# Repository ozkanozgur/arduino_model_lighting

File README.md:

# Model Lighting for Plastic or Diecast models.

You can make lighting for your plastic or diecast models.

Arduino project files, KiCad PCB design files are in this project.

If you don't want to use reed relays, you can replace reed relay with pullup buttons, or pullup short circuits. If you choose pullup buttons or pullup shortcircuits, you need use codes in "without-reed-relays" branch.

P.S.: Please, test circuit on breadboard before make/create final circuit.

### Complete component list is below.

- 1 x Arduino Uno
- 1 x Extra AT Mega 328 P Series Chip
- 12 x White LED (if neccessary for project you can use warm white led.)
- 4 x Red LED
- 4 x Yellow LED
- 10 x 470 ohm SMD Resistor (You can use 330 ohm.)
- 1 x Push Button
- 5 x Magnetic Reed Relay
- 5 x Neodium Magnet (I have used 3mm disc.)
- 2 x 22pF Capasitor
- 1 x 16.000 MHz Crystal
- 1 x 1838B IR Receiver
- 1 x 38KHz IR Remote Controller

### IR Remote Controller Button Functions

- OK => System on/off
- 1 => Parking lights on/off
- 2 => Dipped beam on/off
- 3 => High beam on/off
- 4 => Left turn signal on/off
- 5 => Right turn signal on/off
- 6 => Brake ligth on/off
- 7 => Hazard warning ligths on/off
- 8 => Reverse light on/off

# Plastik yada Diecast Modeller İçin Aydınlatma.

Bu projeyi kullanarak plastik yada diecast modellerinize uzaktan kumanda kontrollü ışıklandırma yapabilirsiniz.

Arduino proje dosyaları ve KiCad baskı devre tasarım dosyaları dahildir.

Eğer reed röleler yerine pullup button yada pullup kısa devre yapmak isterseniz, "without-reed-relays" branchi içerisindeki kodları kullanmanız gerekmektedir.

NOT: Lütfen devrenin baskı halini yapmadan önce breadboard üzerinde testlerinizi yapın.

### Komponent Listesi

- 1 x Arduino Uno
- 1 x Ekstra AT Mega 328 P Serisi Entegre Çip
- 12 x Beyaz LED (Projenize göre gün ışığı led de olabilir.)
- 4 x Kırmızı LED
- 4 x Sarı LED
- 10 x 470 ohm SMD Direnç (330 ohm da kullanılabilir.)
- 1 x Push Button
- 5 x Magnetic Reed Röle
- 5 x Neodium Mıknatıs (Ben 3mm yuvarlak olanlardan kullandım.)
- 2 x 22pF Kondansatör
- 1 x 16.000 MHz Kristal
- 1 x 1838B IR Alıcı
- 1 x 38KHz IR Uzaktan Kumanda

### IR Uzaktan Kumanda DÜğme Fonksiyonları

- OK => Sistem aç/kapat
- 1 => Parklar aç/kapat
- 2 => Kısalar aç/kapat
- 3 => Uzunlar aç/kapat
- 4 => Sol sinyal aç/kapat
- 5 => Sağ sinyal aç/kapat
- 6 => Fren lambası aç/kapat
- 7 => Dörtlüler aç/kapat
- 8 => Geri vites lambası aç/kapat
- Sol Ok => Sol sinyal aç/kapat
- Sağ Ok => Sağ sinyal aç/kapat

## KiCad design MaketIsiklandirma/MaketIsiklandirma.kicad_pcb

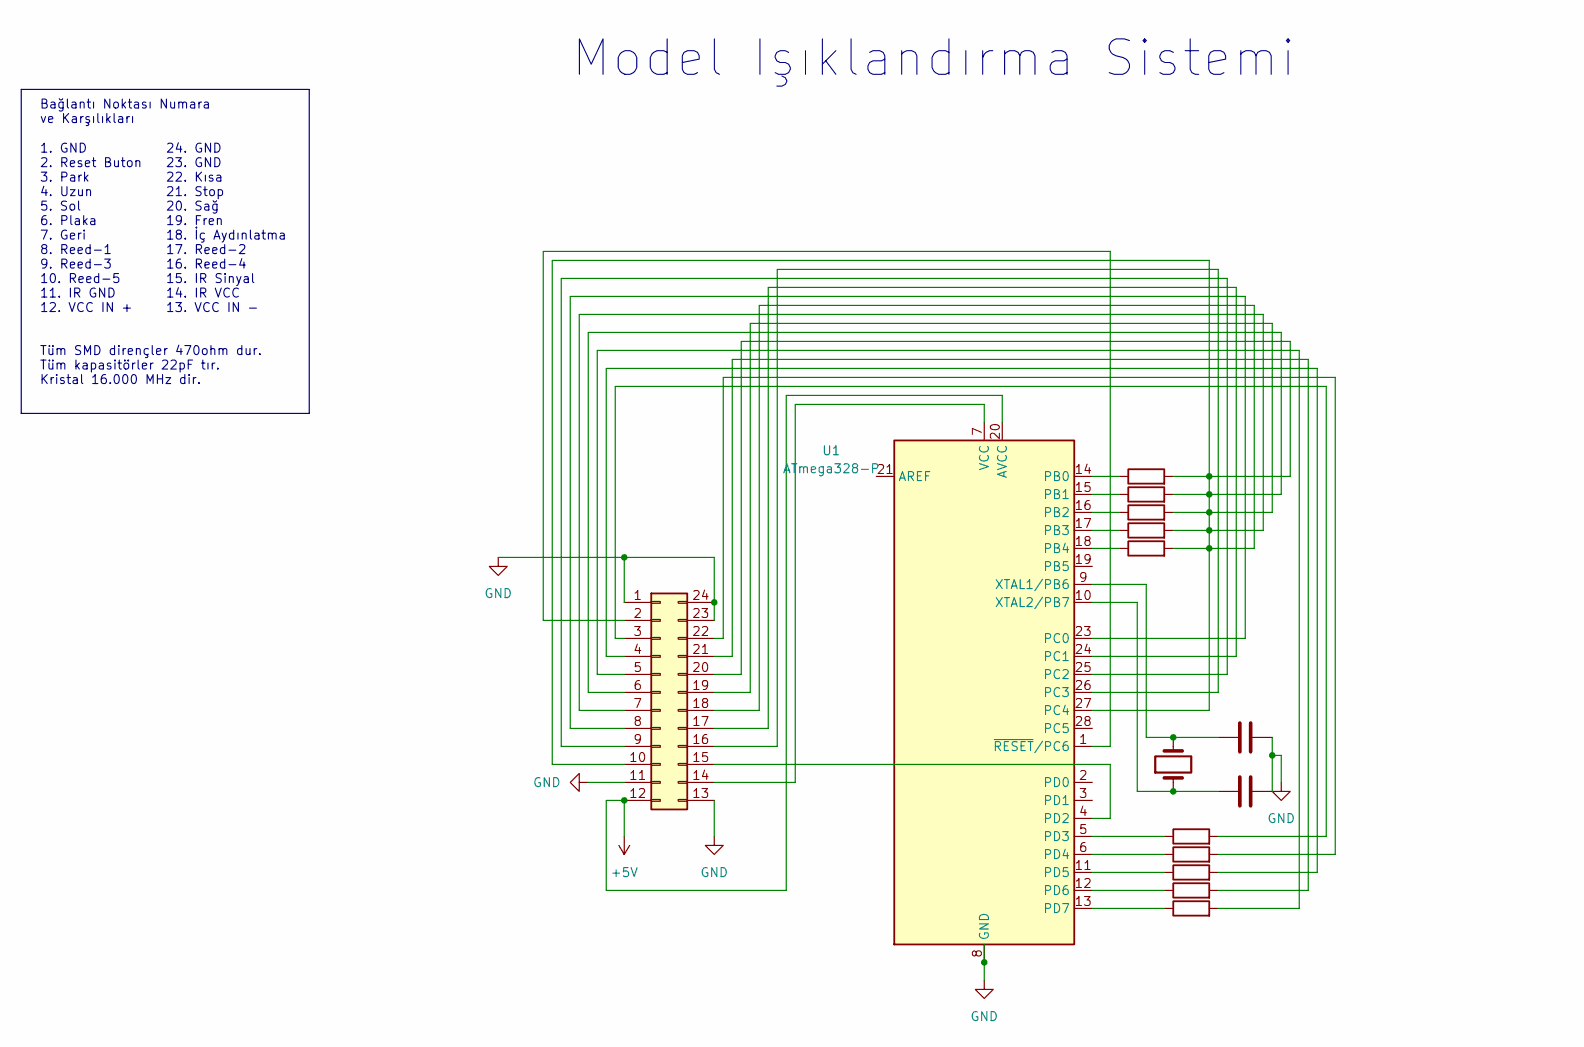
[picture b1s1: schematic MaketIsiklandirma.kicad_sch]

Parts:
C1, C2: C; C_Disc_D8.0mm_W5.0mm_P5.00mm
J3: Conn_02x12_Counter_Clockwise; IDC-Header_2x12_P2.54mm_Vertical
R1, R2, R3, R4, R5, R6, R7, R8, R9, R10: R; R_2512_6332Metric_Pad1.40x3.35mm_HandSolder
U1: ATmega328-P; DIP-28_W7.62mm
Y1: Crystal; Crystal_HC49-U_Vertical

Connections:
+5V: J3.12, U1.20 (AVCC)
unnamed: J3.3, R1.2
unnamed: J3.4, R3.2
unnamed: J3.5, R5.2
unnamed: J3.8, U1.23 (PC0)
unnamed: J3.9, U1.25 (PC2)
unnamed: J3.6, J3.7, J3.10, J3.18, J3.19, J3.20, R6.2, R7.2, R8.2, R9.2, R10.2, U1.27 (PC4)
unnamed: J3.14, U1.7 (VCC)
unnamed: J3.15, U1.4 (PD2)
unnamed: J3.16, U1.26 (PC3)
unnamed: J3.17, U1.24 (PC1)
unnamed: J3.21, R4.2
unnamed: J3.22, R2.2
unnamed: R10.1, U1.14 (PB0)
unnamed: R9.1, U1.15 (PB1)
unnamed: R8.1, U1.16 (PB2)
unnamed: R7.1, U1.17 (PB3)
unnamed: R6.1, U1.18 (PB4)
unnamed: R1.1, U1.5 (PD3)
unnamed: R2.1, U1.6 (PD4)
unnamed: R3.1, U1.11 (PD5)
unnamed: R4.1, U1.12 (PD6)
unnamed: R5.1, U1.13 (PD7)
unnamed: C2.1, U1.9 (XTAL1/PB6), Y1.2
unnamed: C1.1, U1.10 (XTAL2/PB7), Y1.1

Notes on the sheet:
Bağlantı Noktası Numara ve Karşılıkları
24. GND 23. GND 22. Kısa 21. Stop 20. Sağ 19. Fren 18. İç Aydınlatma 17. Reed-2 16. Reed-4 15. IR Sinyal 14. IR VCC 13. VCC IN -
Model Işıklandırma Sistemi
Tüm SMD dirençler 470ohm dur. Tüm kapasitörler 22pF tır. Kristal 16.000 MHz dir.
1. GND 2. Reset Buton 3. Park 4. Uzun 5. Sol 6. Plaka 7. Geri 8. Reed-1 9. Reed-3 10. Reed-5 11. IR GND 12. VCC IN +

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
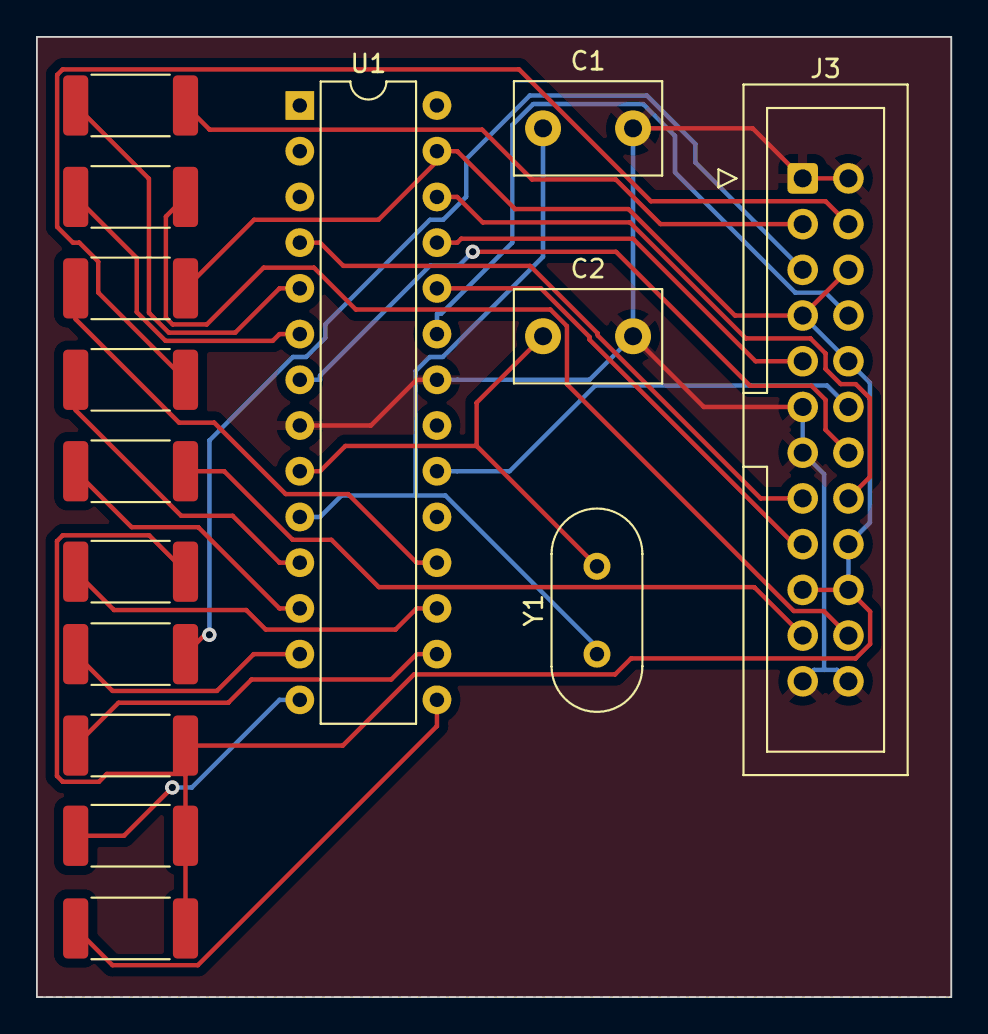
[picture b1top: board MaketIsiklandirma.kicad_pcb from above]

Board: 2 copper layers, 50.8 x 53.3 mm, 15 parts (0 on the bottom side), 26 nets.

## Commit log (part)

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2023-10-06 System done
2023-10-06 Little bug fixes, added README file, and addes KiCad files
2023-10-13 Added functionality to remote controller left and right buttons. They open or close the turn indicators..
2023-10-13 Configured reed relays and reed relays light out pin
2023-10-13 Bugfix v1
2023-10-16 Updates for using it without reed relays.
2023-10-16 README updated.
2023-10-25 Bug fix about short circuits and left and right buttons delay.
